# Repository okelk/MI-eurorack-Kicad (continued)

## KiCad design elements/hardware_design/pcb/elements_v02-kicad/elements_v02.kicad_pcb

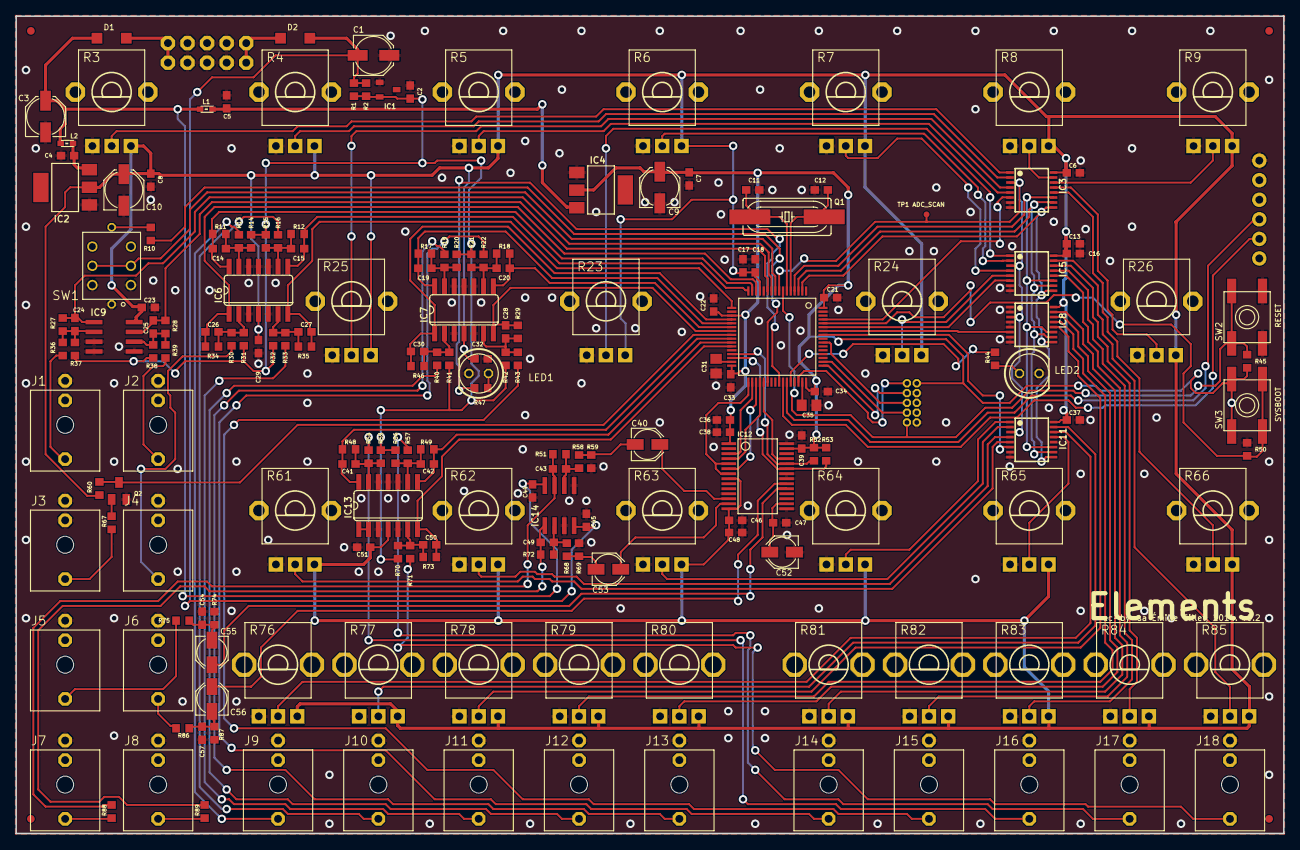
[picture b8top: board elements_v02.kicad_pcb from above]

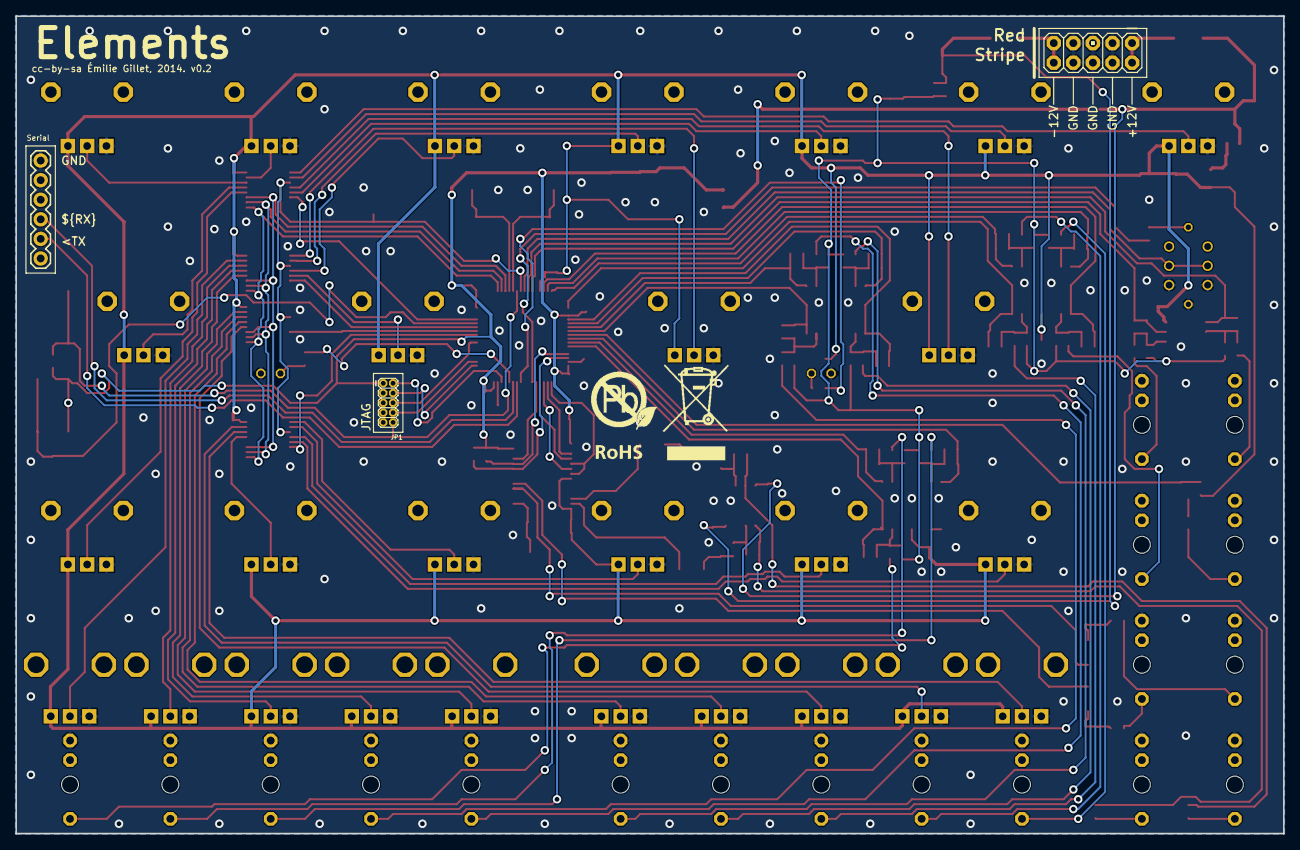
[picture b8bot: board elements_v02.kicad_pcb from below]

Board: 2 copper layers, 164.5 x 106.0 mm, 198 parts (4 on the bottom side), 131 nets.

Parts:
C1, C3, C9, C10: 22u; PANASONIC_C
C2, C4, C5, C6, C7, C8, C13, C16, C18, C21, C22, C23, C29, C32, C33, C34, C37, C38, C39, C44, C45, C46, C47, C51: 100n; C0603
C11, C12, C43, C49: 18p; C0603
C14, C15, C19, C20, C24, C25, C26, C27, C28, C30, C41, C42, C50: 3.3n; C0603
C17, C36, C48: 1u; C0603
C31, C35: 2.2u; C0805
C40, C52, C53, C55, C56: 10u; PANASONIC_B
C54, C57: 220p; C0603
D1, D2: 1N5819HW; SOD123
F1, F2, F3, F4: FIDUCIAL1X2; FIDUCIAL-1X2
IC1: LM4040B10; DBZ_R-PDSO-G3
IC2, IC4: LM1117-3.3; SOT223
IC3, IC5, IC8, IC11: 4051PW; TSSOP16
IC6, IC7, IC13: MCP6004; SO14
IC9: MCP6002; SO08
IC10: STM32F405RGT6; TQFP-10X10-64
IC12: WM8731; SSOP28
IC14: LME49720; SO08
J1, J2, J3, J4, J5, J6, J7, J8, J9, J10, J11, J12, J13, J14, J15, J16, J17, J18: PJ301_THONKICONN6; WQP_PJ_301M6
JP1: M05X2MINIJTAG; 2X5-1.27
JP2: 1X06
JP3: M05X2PTH; AVR_ICSP
L1, L2: 0603
LED1: SSL-LX5093TC; LED5MM
LED2: SSL-LX5093PC; LED5MM
Q1: 8MHz; HC49UP
Q2: MMBT3904; SOT23-BEC
R1, R2, R88, R89: 1.0k; R0603
R3, R4, R5, R6, R7, R8, R9, R23, R24, R25, R26, R61, R62, R63, R64, R65, R66: 10kB; ALPS_POT_VERTICAL_PS
R10: 33; R0603
R11, R12, R17, R18, R28, R29, R35, R46, R48, R49, R73: 20k; R0603
R13, R16, R19, R22, R30, R33, R36, R39, R40, R43, R54, R57, R67, R71: 100k; R0603
R14, R15, R20, R21, R32, R38, R41, R42, R55, R56, R70: 120k; R0603
R27, R51, R59, R69, R72: 47k; R0603
R31: 200k; R0603
R34: 33k; R0603
R37: 180k; R0603
R44, R47, R52, R53: 2.2k; R0603
R45, R50, R60: 10k; R0603
R58, R68, R74, R87: 6.8k; R0603
R75, R86: 36k; R0603
R76, R77, R78, R79, R80, R81, R82, R83, R84, R85: 10kB; ALPS_POT_VERTICAL
SW1: LP4OA1PBCT
SW2, SW3: EVQ-Q2
TP1: ADC_TEST; PAD.03X.03
U$2: ROHS_BIG

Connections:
+3V3: C7.1, C9.+, C21.1, C22.1, C33.1, C34.1, C36.1, C38.1, C39.1, IC4.2, IC10.19, IC10.32, IC10.48, IC10.64, IC12.1, IC12.27, JP1.1, R45.2, R52.2, R53.2, SW3.B, SW3.B'
+3V3_A: C6.1, C8.1, C10.+, C13.1, C16.1, C17.1, C18.1, C23.1, C29.1, C32.1, C37.1, C46.1, C48.1, C51.1, IC2.2, IC3.16, IC5.16, IC6.4, IC7.4, IC8.16, IC9.8, IC10.13, IC11.16, IC12.8, IC12.14, IC13.4, R3.P$1, R4.P$1, R5.P$1, R6.P$1, R7.P$1, R8.P$1, R9.P$1, R23.P$1, R24.P$1, R25.P$1, R26.P$1, R60.2, R61.P$1, R62.P$1, R63.P$1, R64.P$1, R65.P$1, R66.P$1, R76.P$1, R77.P$1, R78.P$1, R79.P$1, R80.P$1, R81.P$1, R82.P$1, R83.P$1, R84.P$1, R85.P$1
ADC_ADDR_0: IC3.11, IC5.11, IC8.11, IC10.4, IC11.11
ADC_ADDR_1: IC3.10, IC5.10, IC8.10, IC10.3, IC11.10
ADC_ADDR_2: IC3.9, IC5.9, IC8.9, IC10.2, IC11.9
ADC_BANK_0: IC10.57, IC11.6
ADC_BANK_1: IC8.6, IC10.58
ADC_BANK_2: IC5.6, IC10.59
ADC_BANK_3: IC3.6, IC10.61
ADC_BLOW_SHAPE: C15.2, IC6.8, IC10.16, R12.1
ADC_BLOW_TIMBRE: C27.2, IC6.7, IC10.17, R35.1
ADC_BOW_TIMBRE: C14.2, IC6.14, IC10.15, R11.1
ADC_BRIGHTNESS: C42.2, IC10.26, IC13.8, R49.1
ADC_DAMPING: C20.2, IC7.8, IC10.22, R18.1
ADC_FM: C25.2, IC9.7, IC10.11, R28.1
ADC_GEOMETRY: C28.2, IC7.7, IC10.23, R29.1
ADC_POSITION: C41.2, IC10.25, IC13.14, R48.1
ADC_POTS: IC3.3, IC5.3, IC8.3, IC10.8, IC11.3, TP1.P$1
ADC_PRESSURE: C26.2, IC6.1, IC10.14, R34.1
ADC_SPACE: C50.2, IC10.27, IC13.7, R73.1
ADC_STRIKE_SHAPE: C30.2, IC7.1, IC10.20, R46.1
ADC_STRIKE_TIMBRE: C19.2, IC7.14, IC10.21, R17.1
ADC_V_OCT: C24.2, IC9.1, IC10.10, R27.1
AREF_-10: C2.1, IC1.2, R1.2, R2.2, R14.2, R15.2, R20.2, R21.2, R31.2, R32.2, R37.2, R38.2, R41.2, R42.2, R55.2, R56.2, R70.2
BOOT_FLASH: IC10.60, R50.2, SW3.A, SW3.A'
GATE: IC10.24, Q2.C, R60.1
GND: C1.+, C2.2, C3.-, C4.2, C5.2, C6.2, C7.2, C8.2, C9.-, C10.-, C11.1, C12.1, C13.2, C16.2, C17.2, C18.2, C21.2, C22.2, C23.2, C29.2, C31.2, C32.2, C33.2, C34.2, C35.2, C36.2, C37.2, C38.2, C39.2, C44.2, C45.1, C46.2, C47.2, C48.2, C51.2, C52.-, C54.2, C57.2, IC1.1, IC2.1, IC3.7, IC3.8, IC4.1, IC5.7, IC5.8, IC6.3, IC6.5, IC6.10, IC6.11, IC6.12, IC7.3, IC7.5, IC7.10, IC7.11, IC7.12, IC8.1, IC8.2, IC8.4, IC8.5, IC8.7, IC8.8, IC9.3, IC9.4, IC9.5, IC10.12, IC10.18, IC10.28, IC10.63, IC11.7, IC11.8, IC11.12, IC12.11, IC12.15, IC12.21, IC12.22, IC12.28, IC13.3, IC13.5, IC13.10, IC13.11, IC13.12, IC14.3, IC14.5, J1.P1, J2.P1, J3.P1, J3.P2, J4.P1, J5.P1, J6.P1, J7.P1, J8.P1, J9.P1, J10.P1, J11.P1, J12.P1, J13.P1, J14.P1, J15.P1, J16.P1, J17.P1, J18.P1, JP1.3, JP1.5, JP1.9, JP2.1, JP3.3, JP3.4, JP3.5, JP3.6, JP3.7, JP3.8, LED1.K, LED2.K, Q2.E, R3.P$3, R4.P$3, R5.P$3, R6.P$3, R7.P$3, R8.P$3, R9.P$3, R23.P$3, R24.P$3, R25.P$3, R26.P$3, R50.1, R59.1, R61.P$3, R62.P$3, R63.P$3, R64.P$3, R65.P$3, R66.P$3, R69.1, R74.1, R76.P$3, R77.P$3, R78.P$3, R79.P$3, R80.P$3, R81.P$3, R82.P$3, R83.P$3, R84.P$3, R85.P$3, R87.1, SW1.L2, SW1.P3, SW1.P6, SW2.A, SW2.A'
I2C_SCL: IC10.29, IC12.24, R52.1
I2C_SDA: IC10.30, IC12.23, R53.1
I2S_LRCK: IC10.33, IC12.5, IC12.7
I2S_MCK: IC10.37, IC12.25
I2S_SCK: IC10.34, IC12.3
I2S_SIN: IC10.35, IC12.6
I2S_SOUT: IC10.36, IC12.4
JTCK: IC10.49, JP1.4
JTDI: IC10.50, JP1.8
JTDO: IC10.55, JP1.6
JTMS: IC10.46, JP1.2
LED_GATE: IC10.38, R10.1
LIN: C56.+, IC12.20
LOUT: C40.+, IC12.12
LOUT_JACK: J8.P3, R89.1
unnamed: J10.P3, R16.2
unnamed: C15.1, IC6.9, R12.2, R15.1, R16.1
unnamed: J13.P3, R19.2
unnamed: J9.P3, R13.2
unnamed: C14.1, IC6.13, R11.2, R13.1, R14.1
unnamed: J2.P3, R39.2
unnamed: C12.2, IC10.5, Q1.2
unnamed: C11.2, IC10.6, Q1.1
unnamed: C19.1, IC7.13, R17.2, R19.1, R20.1
unnamed: J1.P3, R36.2
unnamed: C24.1, IC9.2, R27.2, R36.1, R37.1
unnamed: J14.P3, R22.2
unnamed: C35.1, IC10.47
unnamed: C20.1, IC7.9, R18.2, R21.1, R22.1
unnamed: C25.1, IC9.6, R28.2, R38.1, R39.1
unnamed: J12.P3, R40.2
unnamed: C47.1, C52.+, IC12.16
unnamed: C56.-, C57.1, R86.1, R87.2
unnamed: C31.1, IC10.31
unnamed: J5.P3, R75.2
unnamed: J6.P3, R86.2
unnamed: C54.1, C55.-, R74.2, R75.1
unnamed: C40.-, R58.2, R59.2
unnamed: C30.1, IC7.2, R40.1, R41.1, R46.2
unnamed: C43.1, IC14.6, R51.2, R58.1
unnamed: J11.P3, R33.2
unnamed: C27.1, IC6.6, R32.1, R33.1, R35.2
unnamed: C43.2, IC14.7, R51.1, R88.2
unnamed: J17.P3, R57.2
unnamed: C42.1, IC13.9, R49.2, R56.1, R57.1
unnamed: C53.-, R68.2, R69.2
unnamed: C49.1, IC14.2, R68.1, R72.2
unnamed: C49.2, IC14.1, R72.1, R89.2
unnamed: J18.P3, R71.2
unnamed: C50.1, IC13.6, R70.1, R71.1, R73.2
unnamed: J15.P3, R43.2
unnamed: C28.1, IC7.6, R29.2, R42.1, R43.1
unnamed: R10.2, SW1.L1
unnamed: J16.P3, R54.2
unnamed: C41.1, IC13.13, R48.2, R54.1, R55.1
unnamed: J4.P3, R30.2
unnamed: C26.1, IC6.2, R30.1, R31.1, R34.2
unnamed: J3.P3, R67.1
unnamed: IC13.1, IC13.2
unnamed: IC11.14, R76.P$2
unnamed: IC11.13, R65.P$2
unnamed: IC11.15, R77.P$2
unnamed: IC11.1, R64.P$2
unnamed: IC11.5, R61.P$2
unnamed: IC8.14, R80.P$2
unnamed: IC8.12, R78.P$2
unnamed: IC11.2, R63.P$2
unnamed: IC11.4, R62.P$2
unnamed: IC10.44, R44.1
unnamed: IC3.12, R66.P$2
unnamed: D1.A, JP3.1, JP3.2
unnamed: IC8.15, R81.P$2
unnamed: IC8.13, R79.P$2
unnamed: LED2.A, R44.2
unnamed: LED1.A, R47.2
unnamed: C5.1, IC4.3, L1.2
unnamed: IC3.13, R26.P$2
unnamed: IC3.15, R8.P$2
unnamed: D2.C, JP3.9, JP3.10
unnamed: IC5.12, R82.P$2
unnamed: Q2.B, R67.2
unnamed: IC5.4, R7.P$2
unnamed: IC3.14, R9.P$2
unnamed: IC5.2, R6.P$2
unnamed: IC5.5, R24.P$2
unnamed: IC5.1, R23.P$2
unnamed: IC3.4, R25.P$2
unnamed: IC3.2, R4.P$2
unnamed: IC3.1, R3.P$2
unnamed: IC3.5, R5.P$2
unnamed: IC5.13, R83.P$2
unnamed: IC5.14, R84.P$2
unnamed: IC5.15, R85.P$2
unnamed: IC10.41, R47.1
unnamed: C4.1, IC2.3, L2.2
RESET: IC10.7, JP1.10, R45.1, SW2.B, SW2.B'
RIN: C55.+, IC12.19
ROUT: C53.+, IC12.13
ROUT_JACK: J7.P3, R88.1
RX: IC10.43, JP2.4
SW_GATE: IC10.9, SW1.P2, SW1.P5
TX: IC10.42, JP2.5
VCC: C3.+, C44.1, D1.C, IC14.8, L1.1, L2.1
VEE: C1.-, C45.2, D2.A, IC14.4, R1.1, R2.1
